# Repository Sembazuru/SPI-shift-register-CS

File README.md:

# SPI-shift-register-CS
The concept is to have a way of selecting many SPI devices without eating up an I/O pin for each device's chip select.

Use a shift register chip to "point to" one of many SPI devices, and then use the SPI ~CS signal on the shift register's output enable pin for the SPI data communication.

One technique might be to shift a 1 the number of times equal to the position number of the desired device, then shift the one's complement out. Then procede with the normal SPI transfer as normal using the shift register network's /OE pin as the SPI transfer ~CS pin.

For revision 1 try using MOSI and SCK to shift to the register. So only need 1 extra pin for the latch. Because the latch of 74HCT595 is rising edge triggered, add circuitry to change the MOSI line from pass-through with latch high to serial cascade with latch low. Essentially will act like a standard SPI ~CS pin for using SPI to shift the "address" of the target SPI device into the shift register.

Possible parts:
<ul>
<li>74HC595 - Shift Register Single 8-Bit Serial to Serial/Parallel
<ul><li>https://octopart.com/search?q=74HC595&filter[fields][avg_avail][]=[1%20TO%20*]&view=matrix&filter[fields][specs.mounting_style.value][]=Through%20Hole
<li>Or any equivalent. Must provide tri-state outputs. 74HC family for compatibility with both 3.3V and 5V SPI networks.
</ul><li>74HC257 - Quadruple 2-Line To 1-Line Data Selectors/Multiplexers
<ul><li>https://octopart.com/search?q=74HC257&filter[fields][avg_avail][]=[1%20TO%20*]&view=matrix&filter[fields][specs.mounting_style.value][]=Through%20Hole
<li>Or any equivalent. Tri-state outputs not necessary. 74HC family for compatibility with both 3.3V and 5V SPI networks.
</ul></ul>

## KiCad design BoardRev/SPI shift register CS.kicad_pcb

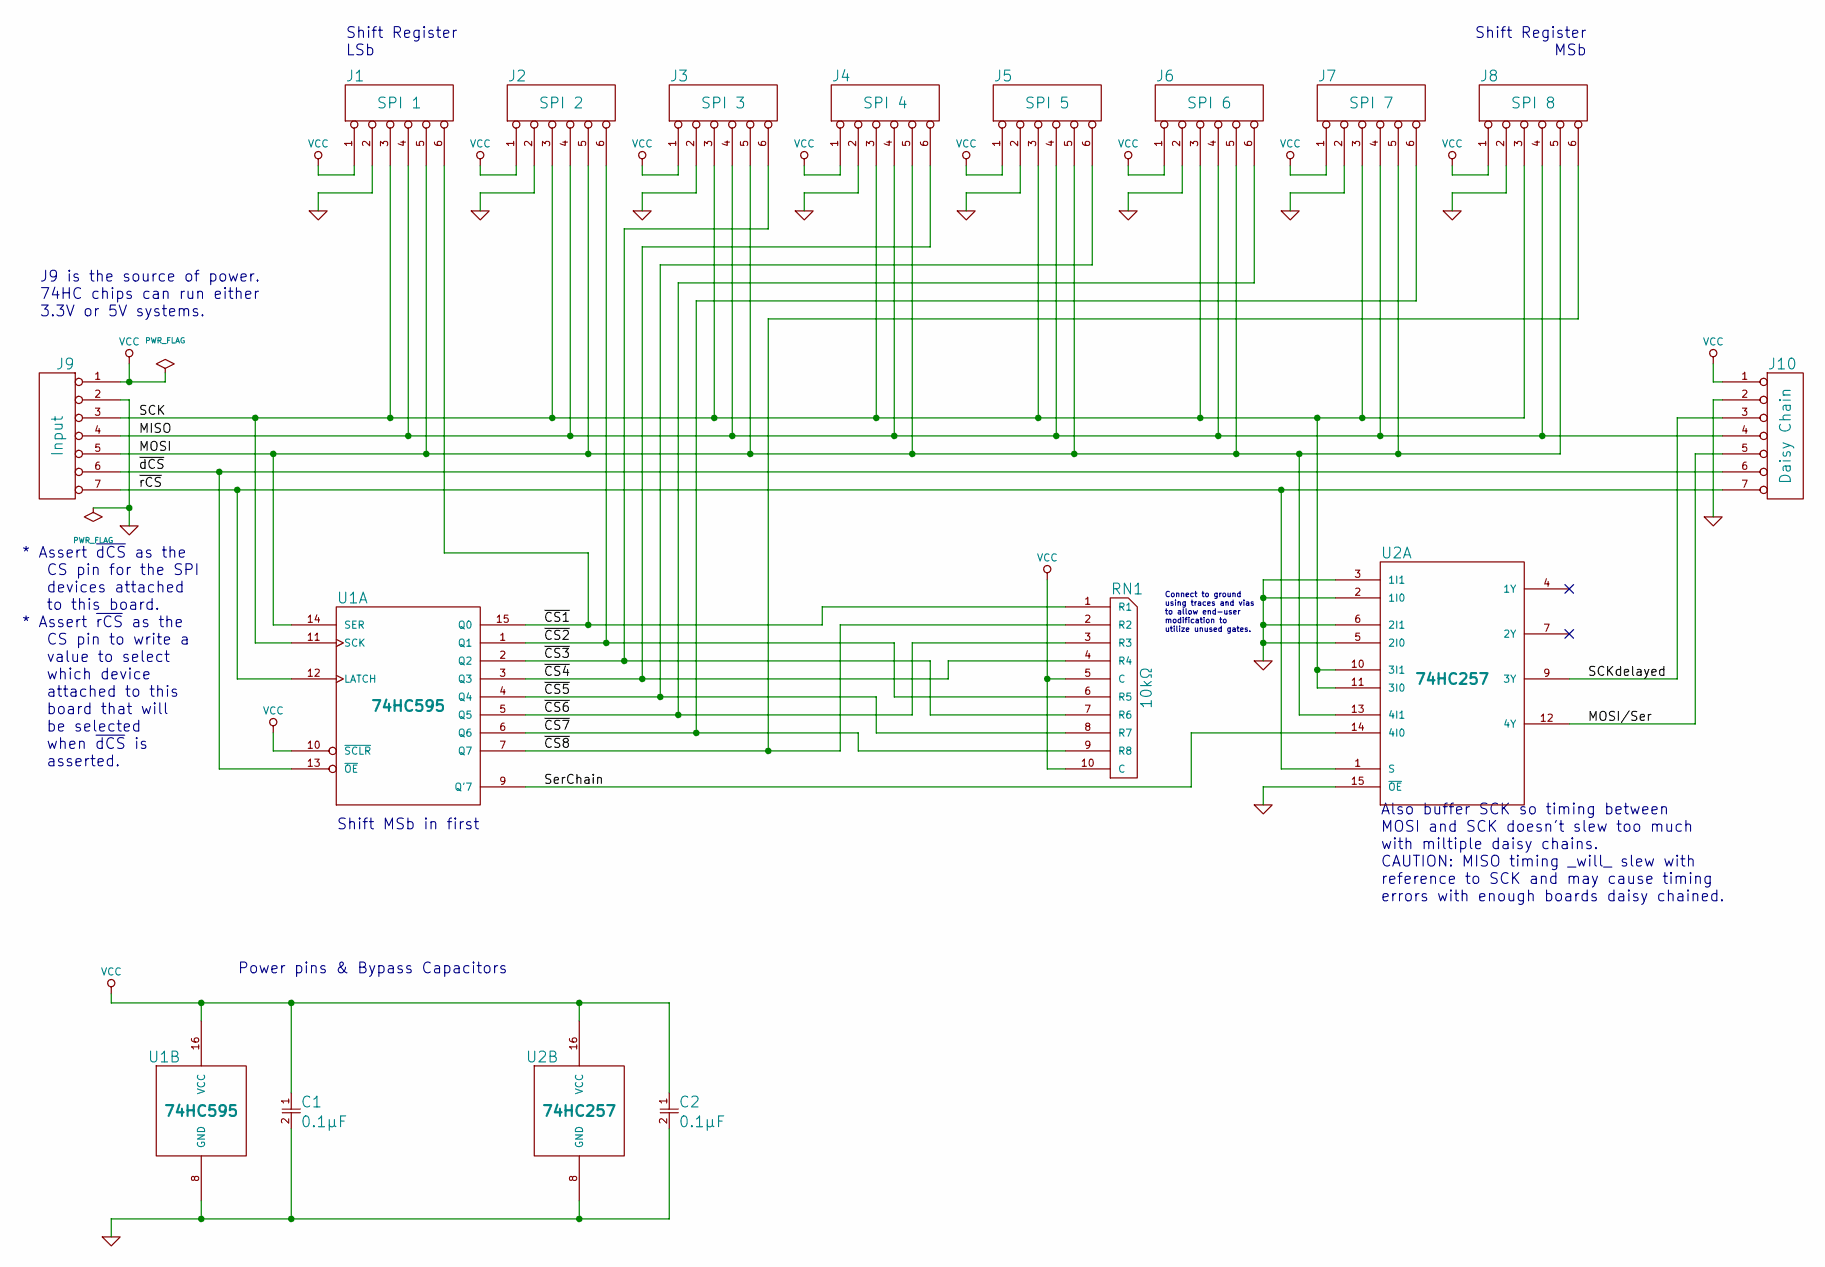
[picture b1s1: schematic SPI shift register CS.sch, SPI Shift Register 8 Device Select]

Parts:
C1, C2: 0.1µF; CAPC1608X90N; MfgPart 06035C104KAT2A
J1, J2, J3, J4, J5, J6, J7, J8: CONN_06; HDRV6W64P254_1X6_1524X254X1016P
J9, J10: CONN_07; HDRV7W64P254_1X7_1778X254X1016P
RN1: 10kΩ; RESCAV_EXBA-10N; MfgPart EXB-A10P103J
U1: 74HC595; SOP65P640X110-16N; MfgPart SN74HC595PWR
U2: 74HC257; SOP65P640X120-16N; MfgPart SN74HC257PW

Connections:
/MISO: J1.4, J2.4, J3.4, J4.4, J5.4, J6.4, J7.4, J8.4, J9.4, J10.4
/MOSI: J1.5, J2.5, J3.5, J4.5, J5.5, J6.5, J7.5, J8.5, J9.5, U1.14 (SER), U2.13 (4I1)
/MOSI/Ser: J10.5, U2.12 (4Y)
/SCK: J1.3, J2.3, J3.3, J4.3, J5.3, J6.3, J7.3, J8.3, J9.3, U1.11 (SCK), U2.10 (3I1), U2.11 (3I0)
/SCKdelayed: J10.3, U2.9 (3Y)
/SerChain: U1.9 (Q'7), U2.14 (4I0)
/~CS1: J1.6, RN1.1 (R1), U1.15 (Q0)
/~CS2: J2.6, RN1.6 (R5), U1.1 (Q1)
/~CS3: J3.6, RN1.7 (R6), U1.2 (Q2)
/~CS4: J4.6, RN1.4 (R4), U1.3 (Q3)
/~CS5: J5.6, RN1.8 (R7), U1.4 (Q4)
/~CS6: J6.6, RN1.3 (R3), U1.5 (Q5)
/~CS7: J7.6, RN1.9 (R8), U1.6 (Q6)
/~CS8: J8.6, RN1.2 (R2), U1.7 (Q7)
/~dCS: J9.6, J10.6, U1.13 (~OE)
/~rCS: J9.7, J10.7, U1.12 (LATCH), U2.1 (S)
GND: C1.2, C2.2, J1.2, J2.2, J3.2, J4.2, J5.2, J6.2, J7.2, J8.2, J9.2, J10.2, U1.8 (GND), U2.2 (1I0), U2.3 (1I1), U2.5 (2I0), U2.6 (2I1), U2.8 (GND), U2.15 (~OE)
VCC: C1.1, C2.1, J1.1, J2.1, J3.1, J4.1, J5.1, J6.1, J7.1, J8.1, J9.1, J10.1, RN1.5 (C), RN1.10 (C), U1.10 (~SCLR), U1.16 (VCC), U2.16 (VCC)

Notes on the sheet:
Also buffer SCK so timing between MOSI and SCK doesn't slew too much with miltiple daisy chains. CAUTION: MISO timing _will_ slew with reference to SCK and may cause timing errors with enough boards daisy chained.
Power pins & Bypass Capacitors
J9 is the source of power. 74HC chips can run either 3.3V or 5V systems.
Shift Register LSb
Shift Register MSb
Shift MSb in first
* Assert ~dCS~ as the CS pin for the SPI devices attached to this board. * Assert ~rCS~ as the CS pin to write a value to select which device attached to this board that will be selected when ~dCS~ is asserted.
Connect to ground using traces and vias to allow end-user modification to utilize unused gates.

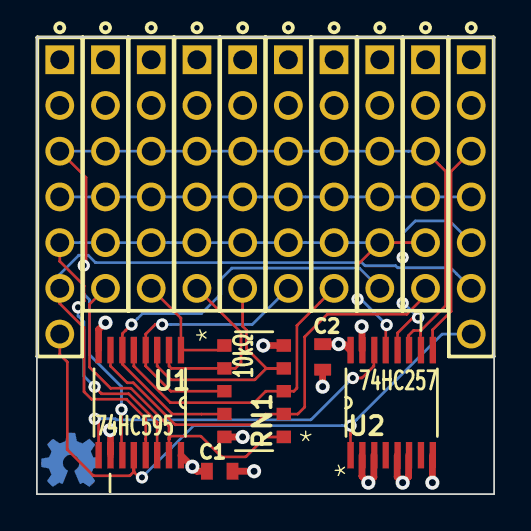
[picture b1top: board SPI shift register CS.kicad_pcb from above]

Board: 4 copper layers, 25.4 x 25.4 mm, 15 parts (0 on the bottom side), 18 nets.

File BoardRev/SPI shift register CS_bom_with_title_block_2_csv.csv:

Source,D:/Libraries/MyDevelopment/KiCad/SPI shift register CS/BoardRev/SPI shift register CS.sch
Kicad Rev,Eeschema 4.0.1-stable
Generated Date,2016-02-26 08:43:33

Title,SPI Shift Register 8 Device Select
Company,Sembazuru Circuits
Revision,2.0.0
Date Issue,2016-02-25
Comment,Intended to be released as OSHW
Comment,v1.0 - First iteration
Comment,v2.0.0 - Convert part numbers and footprints to SMT versions (except for headers).

Reference,Value,Note,CommonPartLibrary,Mfg,MfgPart,Mfg2,Mfg2Part,Library,Library Ref
J10,CONN_07,Daisy Chain,,,,,,NewUnsorted,CONN_07
J9,CONN_07,Input,,,,,,NewUnsorted,CONN_07
J1,CONN_06,SPI 1,,,,,,NewUnsorted,CONN_06
U1,74HC595,,CPL-,Texas Instruments,SN74HC595PWR,,,NewUnsorted,74HC595
U2,74HC257,,CPL-,Texas Instruments,SN74HC257PW,,,NewUnsorted,74HC257
J2,CONN_06,SPI 2,,,,,,NewUnsorted,CONN_06
J3,CONN_06,SPI 3,,,,,,NewUnsorted,CONN_06
J4,CONN_06,SPI 4,,,,,,NewUnsorted,CONN_06
J5,CONN_06,SPI 5,,,,,,NewUnsorted,CONN_06
J6,CONN_06,SPI 6,,,,,,NewUnsorted,CONN_06
J7,CONN_06,SPI 7,,,,,,NewUnsorted,CONN_06
J8,CONN_06,SPI 8,,,,,,NewUnsorted,CONN_06
C1,0.1µF,,CPL-CAP-X7R-0603-100NF-50V,AVX,06035C104KAT2A,Kemet,C0603C104K5RACTU,NewUnsorted,CAP_NP
C2,0.1µF,,CPL-CAP-X7R-0603-100NF-50V,AVX,06035C104KAT2A,Kemet,C0603C104K5RACTU,NewUnsorted,CAP_NP
RN1,10kΩ,,CPL-ARRB-2512-10KOHM-0.062W*,Panasonic,EXB-A10P103J,,,NewUnsorted,RN8BUSDIP

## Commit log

2015-03-01 :lollipop: Added .gitattributes & .gitignore files
2015-03-01 Opened git
    Board rev1 ordered from Bay Area Circuits
2015-03-01 Create README.md
    Was Project concept.TXT
2015-03-01 Delete Project concept.TXT
    Moved to README.md
2015-03-01 Update README.md
    Pretty up the formatting.
2015-03-02 Add *.7z to .gitignore
2015-05-09 Add Board Checkout sketch for Arduino
    Basic sketch to verify board operation and user understanding of
    outputs.
2015-05-09 Update Arduino sketch
    Add sketch identifier serial output to setup().
2015-05-09 Update Arduino sketch
    Corrected some comments.
2015-05-10 Add new Arduino sketch
    Add more practical example sketch. Read 4 thermocouples and show
    readings on 4 OLED displays. Total of 8 SPI devices, only 2 chip select
    pins required.
2015-05-10 Correct Date
    Correct the comment date.
2015-05-12 Create gh-pages branch via GitHub
2015-05-13 Add Fahrenheit display
    Add Fahrenheit so displays show both Celsius and Fahrenheit.
    Change initDisplayCD() to allDisplaysCS() as better inline
    documentation.
    Added more comments to better document intent.
2015-09-05 Renamed PCB source folder.
2015-09-05 Update paths to new Win10 install
2015-09-05 v1.0.1 Add labels to output connectors
2015-09-06 Add som gerber files to repository.
2016-02-25 PCB v1.0.2 - Updated component 3D shapes.
2016-02-26 Initial 1" square SMT version
2016-02-27 PCB v2.0.1 - Tweak routing, and push back slikscreen up 25mil to avoid vias. Ordered first batch (12pcs) from OSHPark.
2017-04-16 collected updates
